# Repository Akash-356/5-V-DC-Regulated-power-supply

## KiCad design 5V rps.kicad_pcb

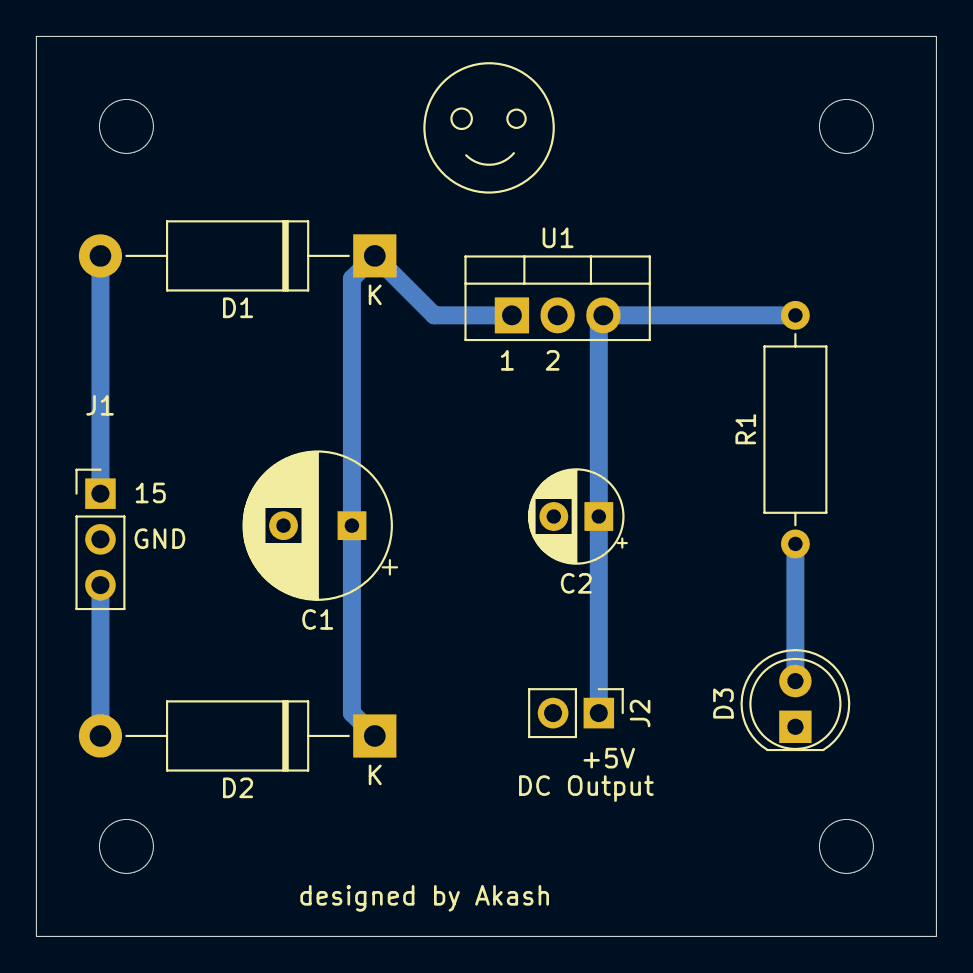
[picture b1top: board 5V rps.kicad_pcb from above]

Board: 2 copper layers, 50.0 x 50.0 mm, 9 parts (0 on the bottom side), 6 nets.

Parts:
C1: 1000uf/25V; CP_Radial_D8.0mm_P3.80mm
C2: 1uf/63V; CP_Radial_D5.0mm_P2.50mm
D1, D2: D; D_DO-15_P15.24mm_Horizontal
D3: LED; LED_D5.0mm
J1: Conn_01x03_Female; PinHeader_1x03_P2.54mm_Vertical
J2: Conn_01x02_Female; PinHeader_1x02_P2.54mm_Vertical
R1: 150E; R_Axial_DIN0309_L9.0mm_D3.2mm_P12.70mm_Horizontal
U1: L7805; TO-220-3_Vertical

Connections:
0(N): C1.2, C2.2, D3.1, J1.2, J2.2, U1.2
15(L1): D1.2, J1.1
15(L2): D2.2, J1.3
+5VDC: C2.1, J2.1, R1.2, U1.3
unnamed: C1.1, D1.1, D2.1, U1.1
unnamed: D3.2, R1.1

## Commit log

2026-03-03 Add files via upload
    This project involves the design and PCB implementation of a regulated 5V DC power supply using KiCad. The system converts an unregulated DC input (or stepped-down AC) into a stable and constant 5V D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
    The complete design includes:
    1.Schematic capture
    2.PCB layout design
    3.Component placement and routing
    4.Design rule checking (DRC)
